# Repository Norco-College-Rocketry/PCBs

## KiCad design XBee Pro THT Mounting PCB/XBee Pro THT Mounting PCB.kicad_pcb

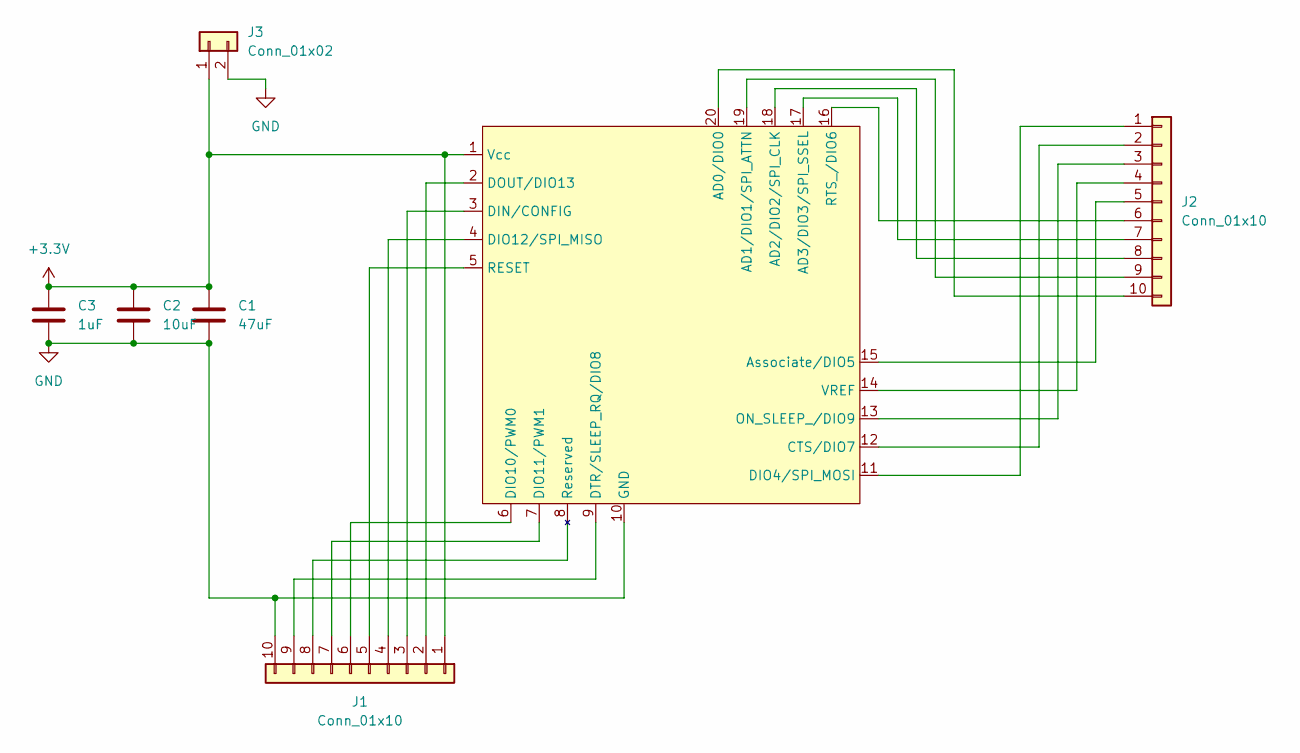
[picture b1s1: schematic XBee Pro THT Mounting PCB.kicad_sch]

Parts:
C1: 47uF; C_1210_3225Metric_Pad1.33x2.70mm_HandSolder
C2: 10uF; C_1210_3225Metric_Pad1.33x2.70mm_HandSolder
C3: 1uF; C_1210_3225Metric_Pad1.33x2.70mm_HandSolder
J1, J2: Conn_01x10; PinHeader_1x10_P2.54mm_Vertical
J3: Conn_01x02; PinHeader_1x02_P2.54mm_Vertical
XBee1: XBee Pro THT Double

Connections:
+3.3V: C1.1, C2.1, C3.1, J1.1, J3.1, XBee1.1 (Vcc)
GND: C1.2, C2.2, C3.2, J1.10, J3.2, XBee1.10 (GND)
unnamed: J1.2, XBee1.2 (DOUT/DIO13)
unnamed: J1.3, XBee1.3 (DIN/CONFIG)
unnamed: J1.4, XBee1.4 (DIO12/SPI_MISO)
unnamed: J1.5, XBee1.5 (RESET)
unnamed: J1.6, XBee1.6 (DIO10/PWM0)
unnamed: J1.7, XBee1.7 (DIO11/PWM1)
unnamed: J1.9, XBee1.9 (DTR/SLEEP_RQ/DIO8)
unnamed: J2.1, XBee1.11 (DIO4/SPI_MOSI)
unnamed: J2.2, XBee1.12 (CTS/DIO7)
unnamed: J2.3, XBee1.13 (ON_SLEEP_/DIO9)
unnamed: J2.4, XBee1.14 (VREF)
unnamed: J2.5, XBee1.15 (Associate/DIO5)
unnamed: J2.6, XBee1.16 (RTS_/DIO6)
unnamed: J2.7, XBee1.17 (AD3/DIO3/SPI_SSEL)
unnamed: J2.8, XBee1.18 (AD2/DIO2/SPI_CLK)
unnamed: J2.9, XBee1.19 (AD1/DIO1/SPI_ATTN)
unnamed: J2.10, XBee1.20 (AD0/DIO0)

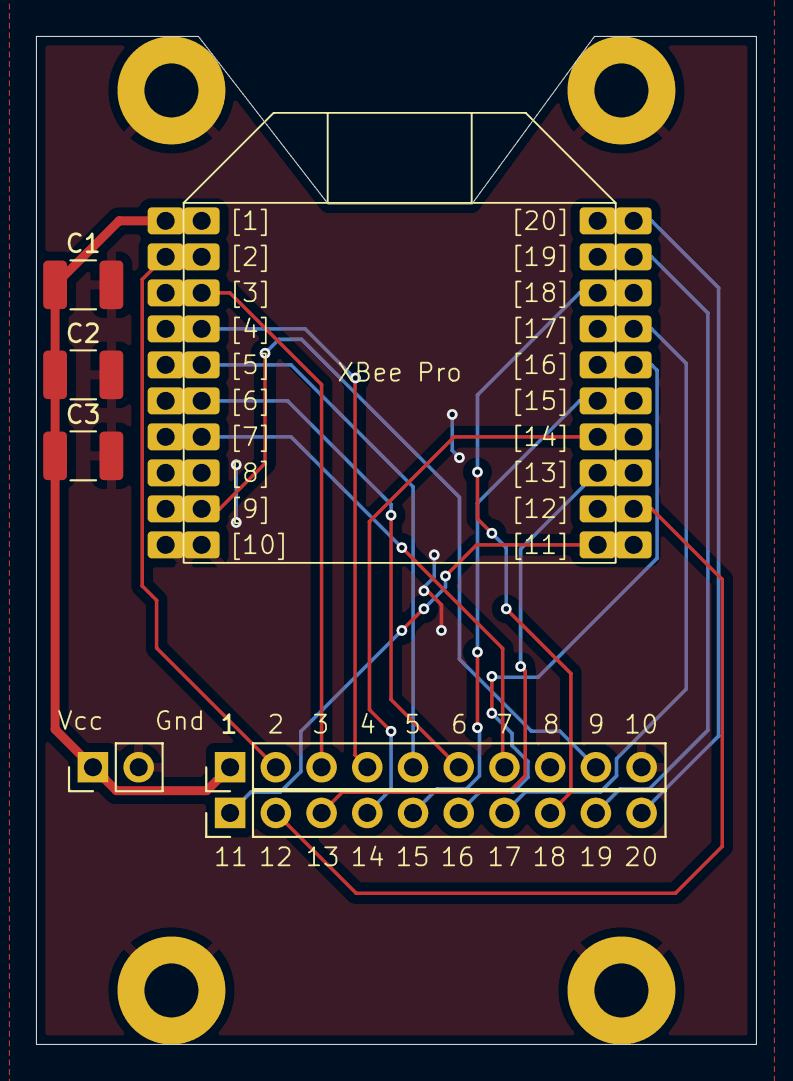
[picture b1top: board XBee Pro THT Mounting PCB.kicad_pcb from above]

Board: 4 copper layers, 40.0 x 56.0 mm, 7 parts (0 on the bottom side), 19 nets.

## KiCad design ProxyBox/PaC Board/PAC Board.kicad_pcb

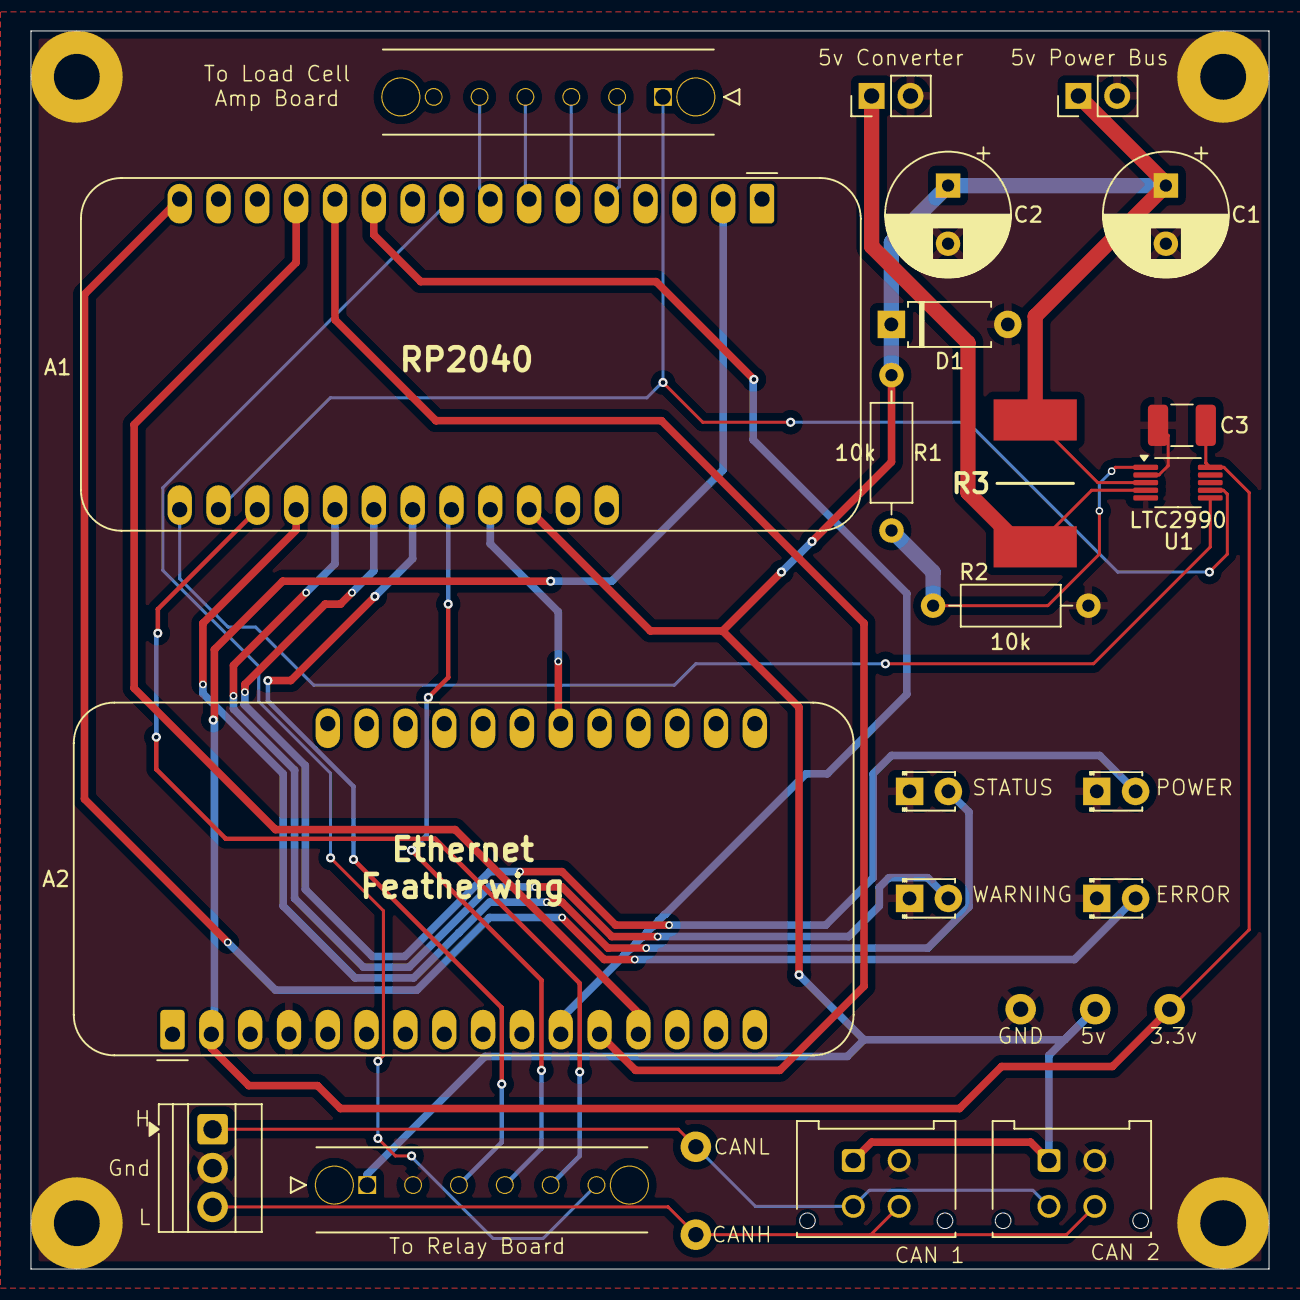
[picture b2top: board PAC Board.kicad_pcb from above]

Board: 2 copper layers, 81.0 x 81.0 mm, 30 parts (0 on the bottom side), 25 nets.

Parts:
A1: Adafruit_Feather_RP2040_CANBUS; Adafruit_Feather
A2: Adafruit_Featherwing_Ethernet; Adafruit_Feather
C1, C2: 680uF; CP_Radial_D8.0mm_P3.80mm
C3: 0.1uf; C_1210_3225Metric_Pad1.33x2.70mm_HandSolder
D1: D; D_A-405_P7.62mm_Horizontal
D3, D4, D5, D6: LED; LED_D1.8mm_W3.3mm_H2.4mm
J1: Screw_Terminal_01x03; TerminalBlock_Xinya_XY308-2.54-3P_1x03_P2.54mm_Horizontal
J2, J7: Conn_01x04; Molex_Micro-Fit_3.0_43045-0412_2x02_P3.00mm_Vertical
J3, J4: Conn_01x06; Molex_Micro-Fit_3.0_43650-0619_1x06_P3.00mm_Vertical
J5, J8, J9, J10, J11: Conn_01x01_Socket; OD_2 ID_1 Circ THT Wire Solder Point
J5#2, J6, J13, J16: Conn_01x01_Socket; M3 Plated Screwhole
J14, J15: Conn_01x02; PinHeader_1x02_P2.54mm_Vertical
R1, R2: 10k; R_Axial_DIN0207_L6.3mm_D2.5mm_P10.16mm_Horizontal
R3: 1m; RESC10052X50N
U1: LTC2990; MSOP-10_3x3mm_P0.5mm

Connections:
5v: A1.26 (USB), C1.1, C2.1, D1.1 (K), J2.1, J3.1, J5.1, J7.1, J15.1, R1.1, R3.1, U1.3 (V3)
5v in: J14.1, R3.2, U1.4 (V4)
GND: A2.4 (GND), C1.2, C2.2, C3.2, D1.2 (A), D3.1 (K), D4.1 (K), D5.1 (K), D6.1 (K), J1.2 (GND), J2.2, J3.2, J5#2.1, J6.1, J7.2, J10.1, J13.1, J14.2, J15.2, J16.1, R2.2, U1.2 (V2), U1.5 (GND)
unnamed: A1.2 (3V3), A2.2 (3V3), C3.1, J11.1, U1.10 (VCC)
unnamed: A1.5 (A0), J4.2
unnamed: A1.6 (A1), J4.3
unnamed: A1.7 (A2), J4.4
unnamed: A1.8 (A3), J4.5
unnamed: J1.1 (CANH), J2.3, J7.3, J9.1
unnamed: J1.3 (CANL), J2.4, J7.4, J8.1
unnamed: A1.16 (D4), D6.2 (A)
unnamed: A1.19 (D5), J3.5
unnamed: A1.20 (D6), D3.2 (A)
unnamed: A1.21 (D9), D4.2 (A)
unnamed: A1.22 (D10), D5.2 (A)
unnamed: A1.23 (D11), J3.3
unnamed: A1.24 (D12), J3.4
unnamed: A1.25 (D13), A2.22 (CS)
unnamed: A1.9 (D24), J3.6
unnamed: A1.13 (MISO), A2.13 (MISO)
unnamed: A1.12 (MOSI), A2.12 (MOSI)
unnamed: A1.11 (SCK), A2.11 (SCK)
unnamed: A1.18 (SCL), J4.1, U1.7 (SCL)
unnamed: A1.17 (SDA), U1.6 (SDA)
unnamed: R1.2, R2.1, U1.1 (V1)

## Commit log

2025-05-05 Create PaC Board
2025-05-06 Create s
